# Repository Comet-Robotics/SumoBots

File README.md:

# SumoBots @ UTD
Main repository for firmware of different robot sumo designs

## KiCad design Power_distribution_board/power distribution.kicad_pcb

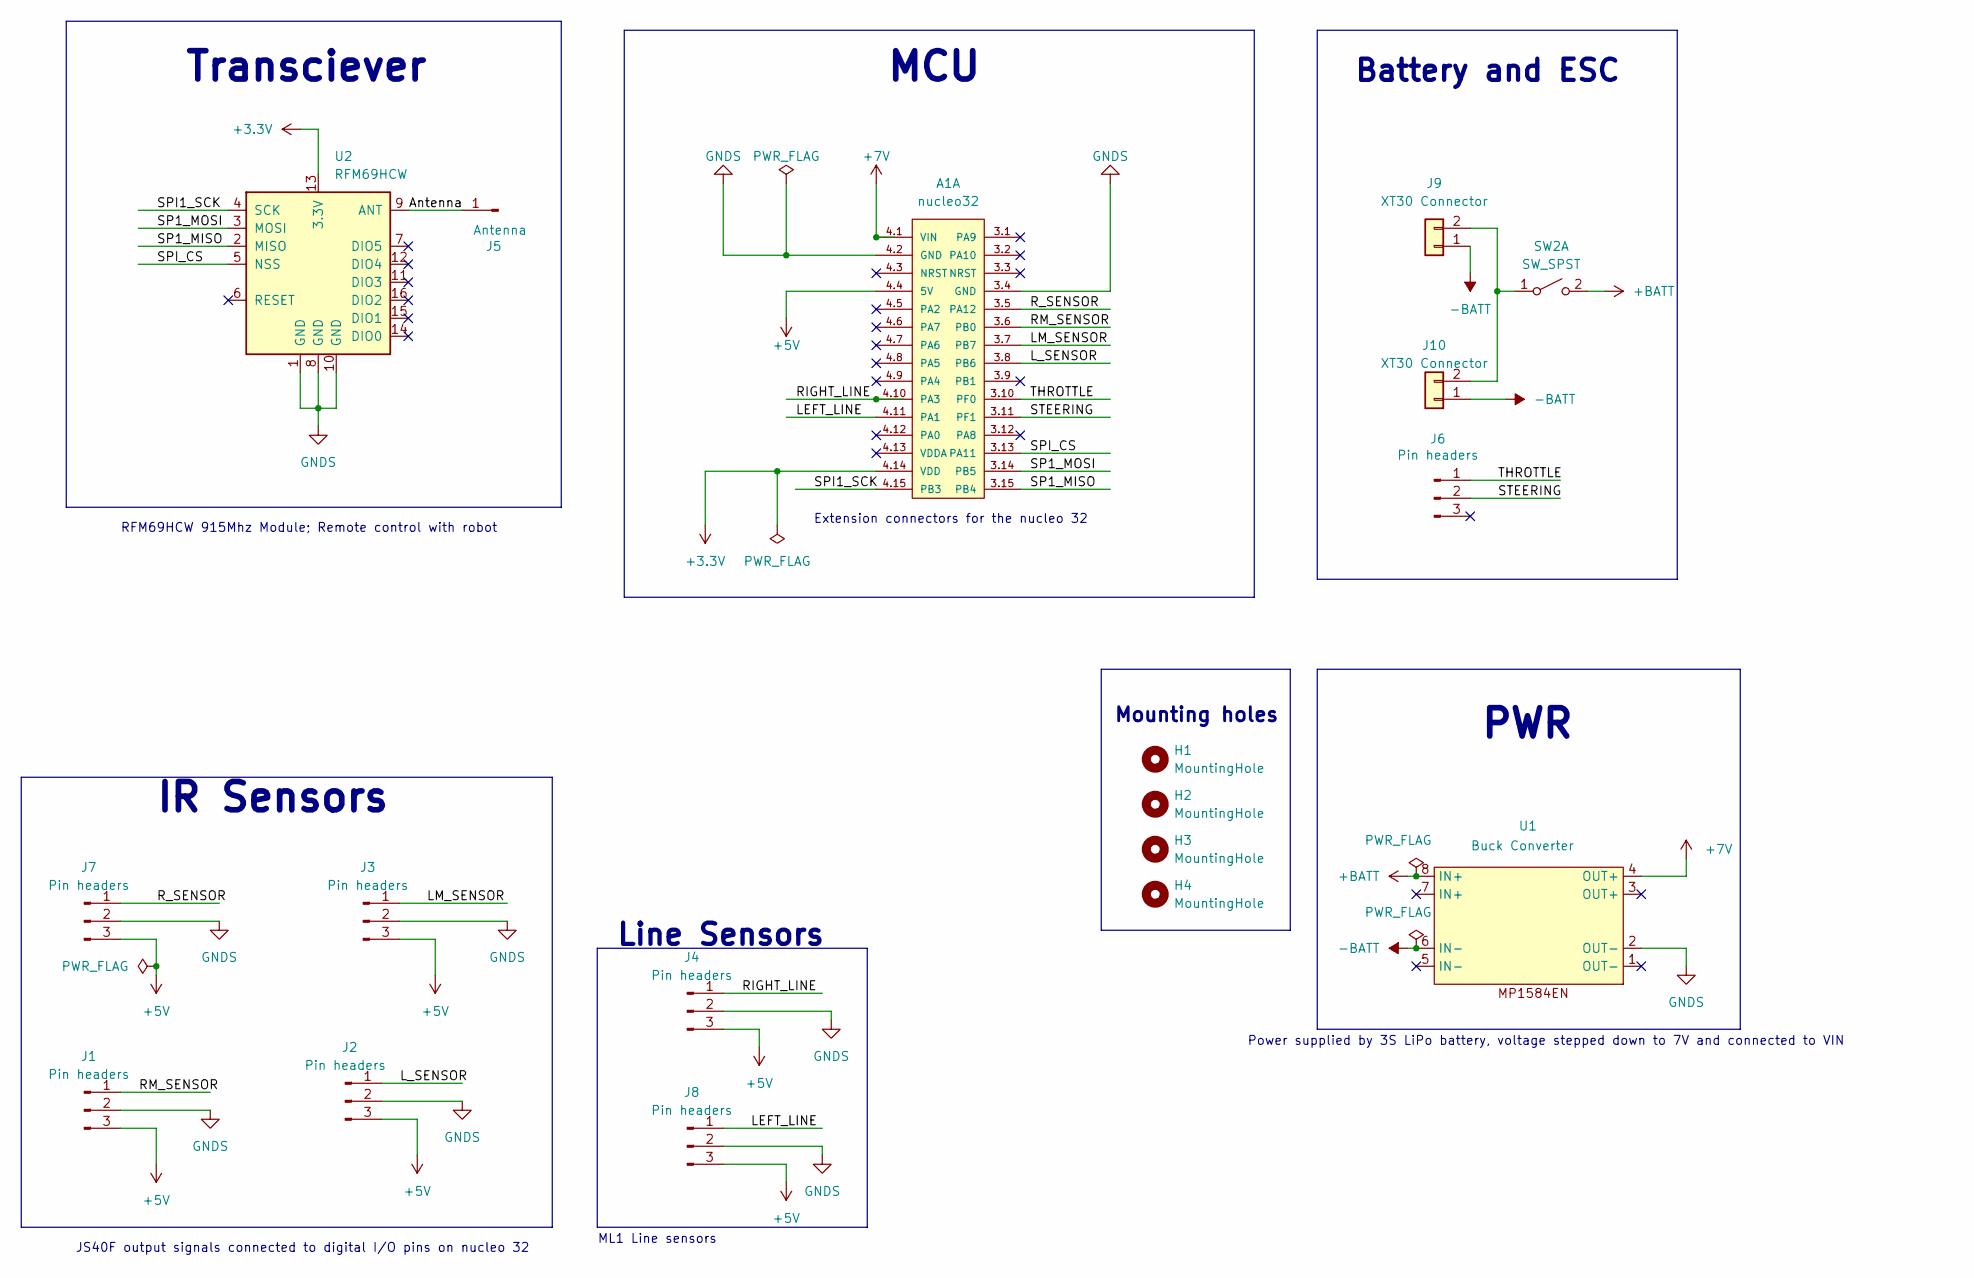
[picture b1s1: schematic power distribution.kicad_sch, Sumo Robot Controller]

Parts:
A1: nucleo32; PARTREV 3
H1, H2, H3, H4: MountingHole; MountingHole_2.2mm_M2
J1, J2, J3, J4, J6, J7, J8: Pin headers; PinHeader_1x03_P2.54mm_Vertical
J5: Antenna; SolderWire-0.1sqmm_1x01_D0.4mm_OD1mm
J9, J10: XT30 Connector; AMASS_XT30PW-M_1x02_P2.50mm_Horizontal
SW2: SW_SPST; GH36P010001_APM
U1: Buck Converter
U2: RFM69HCW; HOPERF_RFM69HW

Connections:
+3.3V: A1.4.14 (VDD), U2.13 (3.3V)
+5V: A1.4.4 (5V), J1.3, J2.3, J3.3, J4.3, J7.3, J8.3
+7V: A1.4.1 (VIN), U1.4 (OUT+)
+BATT: SW2.2 (B), U1.8 (IN+)
-BATT: J9.1, J10.1, U1.6 (IN-)
/Antenna: J5.1, U2.9 (ANT)
/LEFT_LINE: A1.4.11 (PA1), J8.1
/LM_SENSOR: A1.3.7 (PB7), J3.1
/L_SENSOR: A1.3.8 (PB6), J2.1
/RIGHT_LINE: A1.4.10 (PA3), J4.1
/RM_SENSOR: A1.3.6 (PB0), J1.1
/R_SENSOR: A1.3.5 (PA12), J7.1
/SP1_MISO: A1.3.15 (PB4), U2.2 (MISO)
/SP1_MOSI: A1.3.14 (PB5), U2.3 (MOSI)
/SPI1_SCK: A1.4.15 (PB3), U2.4 (SCK)
/SPI_CS: A1.3.13 (PA11), U2.5 (NSS)
/STEERING: A1.3.11 (PF1), J6.2
/THROTTLE: A1.3.10 (PF0), J6.1
GNDS: A1.3.4 (GND), A1.4.2 (GND), J1.2, J2.2, J3.2, J4.2, J7.2, J8.2, U1.2 (OUT-), U2.1 (GND), U2.8 (GND), U2.10 (GND)
unnamed: J9.2, J10.2, SW2.1 (A)

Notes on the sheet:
RFM69HCW 915Mhz Module; Remote control with robot
JS40F output signals connected to digital I/O pins on nucleo 32
Extension connectors for the nucleo 32
MCU
ML1 Line sensors
Line Sensors
Battery and ESC
Power supplied by 3S LiPo battery, voltage stepped down to 7V and connected to VIN
Transciever
IR Sensors
Mounting holes
PWR

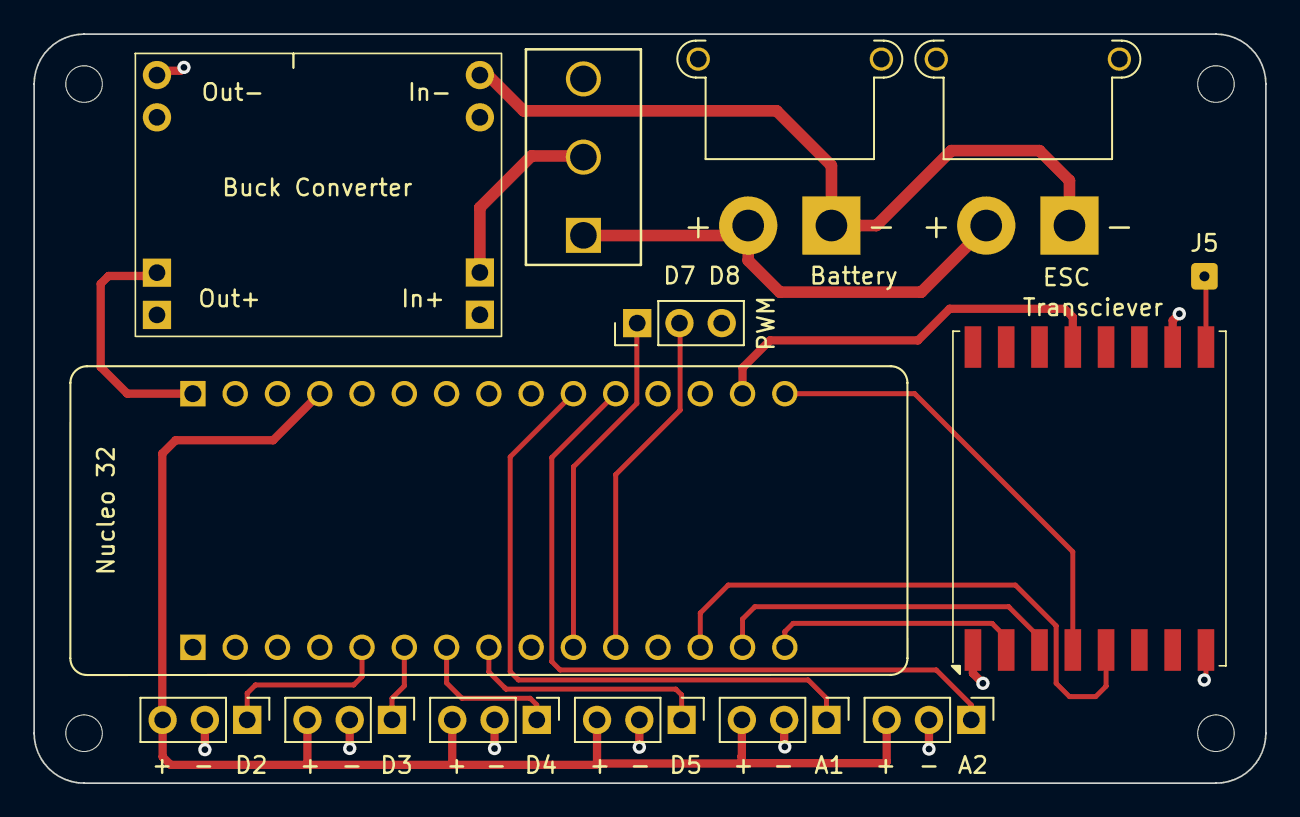
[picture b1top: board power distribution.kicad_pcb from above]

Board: 2 copper layers, 74.0 x 45.0 mm, 18 parts (0 on the bottom side), 20 nets.

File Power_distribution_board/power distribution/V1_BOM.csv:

Reference,Value,Datasheet,Footprint,Qty,DNP
A1,nucleo32,,NUCLEO-F031K6:nucleo32,1,
"J1,J2,J3,J4,J6,J7,J8",Pin headers,~,Connector_PinHeader_2.54mm:PinHeader_1x03_P2.54mm_Vertical,7,
"J9,J10",XT30 Connector ,~,Connector_AMASS:AMASS_XT30PW-M_1x02_P2.50mm_Horizontal,2,
SW2,SW_DPST_x2,~,Button_Switch_THT:SW_CK_JS202011CQN_DPDT_Straight,1,
U1,Buck Converter,,Buck Converter:Buck Converter,1,
U2,RFM69HCW,https://www.hoperf.com/data/upload/portal/20181127/5bfcb8284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,RF_Module:HOPERF_RFM69HW,1,

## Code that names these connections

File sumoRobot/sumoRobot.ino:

/* 
  This program contains the Firmware for the 1kg class Comet Robotics UTD 
  UTD Sumo robot. 
*/ 


#include <Servo.h> 


// Pin Definitions
#define OS1  PB7    //Opponent sensor 1                 CN9 1
#define OS2  PB6    //Opponent sensor 2                 CN9 2
#define LS1  PA10   //Pin number for line sensor 1      CN9 3
#define LS2  PB3    //Pin number for line sensor 2      CN9 4
#define M1 PB5     //Pin number for motor 1            CN9 5
#define M2 PB4      //Pin number for motor 2           CN9 6
int op1;            //Reading from left opponent sensor 
int op2;            //Reading from right opponent sensor 
int ln1;            //Reading from line sensor
int ln2;            //Reading from line sensor 2
volatile bool line_hit; 

Servo M1_Steering; 
Servo M2_Throttle; 

void lineHit1();
void lineHit2(); 
bool isLineHit();
void DRIVE(int speed1, int speed2); 
void Stop(); 
void setMotors();
void setSensors(); 
void armESC(); 

void setup() {
  Serial.begin(9600);
  Serial.println("Starting...");
  setSensors();
  setMotors();
  armESC();
  
  delay(5000);  //Wait for 5 seconds
}

void loop() {
  ln1 = digitalRead(LS1);
  ln2 = digitalRead(LS2);
  op1 = digitalRead(OS1);
  op2 = digitalRead(OS2);
  seen_left = 0;

  /*
  Serial.print("OP1: "); 
  Serial.println(op1);
  Serial.print("OP2: "); 
  Serial.println(op2);
  */

  if(isLineHit())
  {
    /*
    Serial.print("Ln1: "); 
    Serial.println(ln1);
    Serial.print("Ln2: "); 
    Serial.println(ln2);
    */

    Stop();
    //Drive backwards
    DRIVE(1500,1300);
    delay(200);

    //Turn around
    DRIVE(1700, 1500);
    delay(500);
  }
  else
  {
    if (op1 && op2)  //Go forwards while opponent seen in both sensors.
    {
      DRIVE(1500,1600);
    }
    else if (!op1 && op2)  //Go forwards and slightly right while opponent seen by only left sensor
    {
      seen_left = 1;
      DRIVE(1600,1500);
    }
    else if (op1 && !op2)  //Go forwards and slightly left while opponent seen by only right sensor
    {
      seen_right = 0;
      DRIVE(1400,1500);
    }
    else //Turn and move forward slightly if the opponent is not seen
    {
      if(seen_left){
        DRIVE(1350,1500);
      }
      else {
        DRIVE(1650,1500);
      }
      delay(500);
      Stop();
      delay(200);
    }
  }
}

bool isLineHit() {
  return line_hit;
}

//Updates line_hit on an interrupt
void lineHit1() {
  line_hit = digitalRead(ln1);
}
void lineHit2() {
  line_hit = digitalRead(ln2);
}

//1000-Minimum  1500-Neutral  2000-Maximum
void DRIVE(int speed1, int speed2) {
  M1_Steering.writeMicroseconds(speed1);
  M2_Throttle.writeMicroseconds(speed2);
}

void Stop() {
  DRIVE(1500,1500);
  delay(150);
}

void setMotors() { 
  pinMode(M1, OUTPUT);
  pinMode(M2, OUTPUT);
  M2_Throttle.attach(M2, 1000, 2000); 
  M1_Steering.attach(M1, 1000, 2000);
}

void setSensors() { 
  pinMode(OS1, INPUT);
  pinMode(OS2, INPUT);
  pinMode(LS1, INPUT);
  pinMode(LS2, INPUT);
  attachInterrupt(digitalPinToInterrupt(LS1), lineHit1,CHANGE);
  attachInterrupt(digitalPinToInterrupt(LS2), lineHit2,CHANGE);
}

void armESC() { 
  
  delay(10);
  for (int i = 60; i < 80; i++) { 
    M2_Throttle.write(i);
    M1_Steering.write(i);
    Serial.println(i);
    delay(500); 
  }

  //delay(10);
  //LeftMotor.write(68);
  //RightMotor.write(68);
  delay(300);
}

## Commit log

2024-02-20 Update sumoRobot.ino
    Fixed lineHit function
2024-03-08 Modified pin mappings, altered Drive function
2024-03-09 Updated drive function, Robot should move as intended
2024-03-19 Update sumoRobot.ino
    Swapped the steering/throttle motor names
2024-03-26 Updated interrupts
    Interrupts now update a boolean variable that is then checked in the main loop.
2024-04-09 Update sumoRobot.ino
    Bot now 'remembers' which direction it last saw the opponent and turns in that direction when not detecting anything
2024-04-16 Rename RFM69-master.zip to RFM69-master(SparkFunTransceiverLibraryForArduino).zip
2024-07-02 imported kiCAD project files
2024-07-02 Consolidated firmware into its own directory
2024-07-02 remove duplicate folders
2024-07-02 removed duplicate folders in power distribution
2024-07-02 removed duplicate sumoRobot.ino
2024-07-06 added new switch footprint, update gerbers
2024-09-18 Create Getting-Started
    Included tutorial on setting up VSCode, PlatformIO, and Git
2024-09-18 Create Getting-Started.md
    Added tutorial for installing VSCode, PlatformIO, and Git
2024-09-23 update backups
2024-09-23 test
2024-09-24 deleted garbage file
